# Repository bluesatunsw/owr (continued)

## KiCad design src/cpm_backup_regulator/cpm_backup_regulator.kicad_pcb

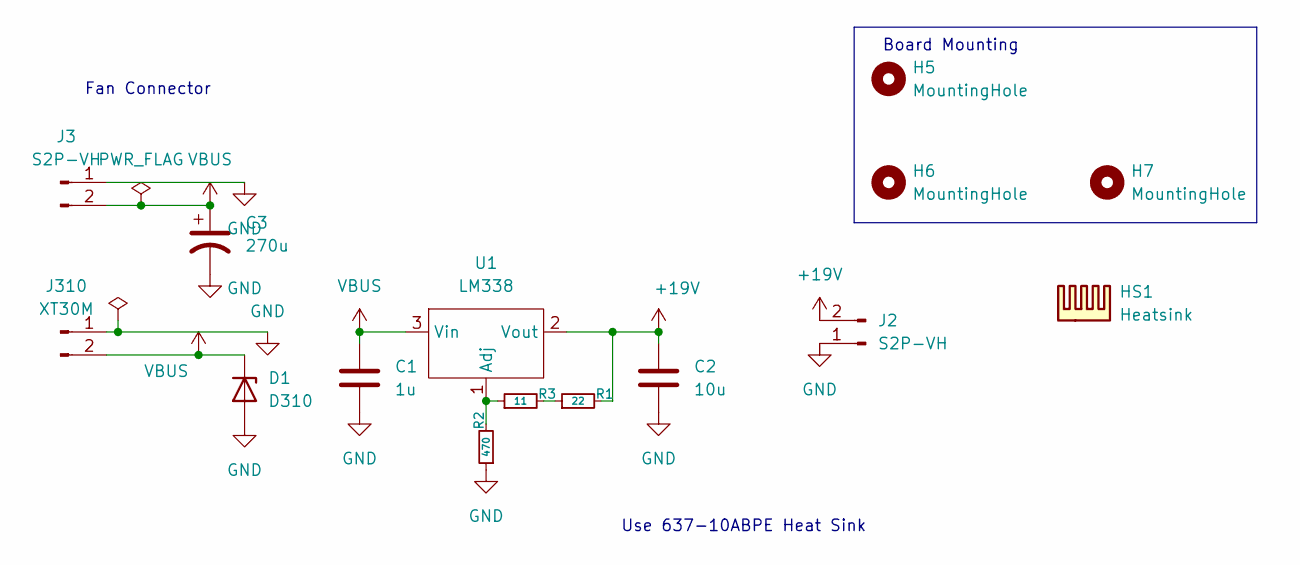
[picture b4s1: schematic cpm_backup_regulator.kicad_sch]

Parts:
C1: 1u; C_0805_2012Metric
C2: 10u; C_1210_3225Metric
C3: 270u; CP_Elec_10x10
D1: D310; D_SMF
H5, H6, H7: MountingHole; M2.5_Internal
HS1: Heatsink; Heatsink_Fischer_SK129-STS_42x25mm_2xDrill2.5mm
J2: S2P-VH; B2P-VH
J3: S2P-VH; BM02B-PASS
J310: XT30M; AMASS_XT30PW-M_1x02_P2.50mm_Horizontal
R1: 22; C_0402_1005Metric
R2: 470; C_0402_1005Metric
R3: 11; C_0402_1005Metric
U1: LM338; TO-220F-3_Vertical

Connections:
+19V: C2.1, J2.2, R1.2, U1.2 (Vout)
GND: C1.2, C2.2, C3.2, D1.2 (A), J2.1, J3.1, J310.1, R2.1
unnamed: R1.1, R3.2
unnamed: R2.2, R3.1, U1.1 (Adj)
VBUS: C1.1, C3.1, D1.1 (K), J3.2, J310.2, U1.3 (Vin)

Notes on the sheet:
Fan Connector
Board Mounting
Use 637-10ABPE Heat Sink

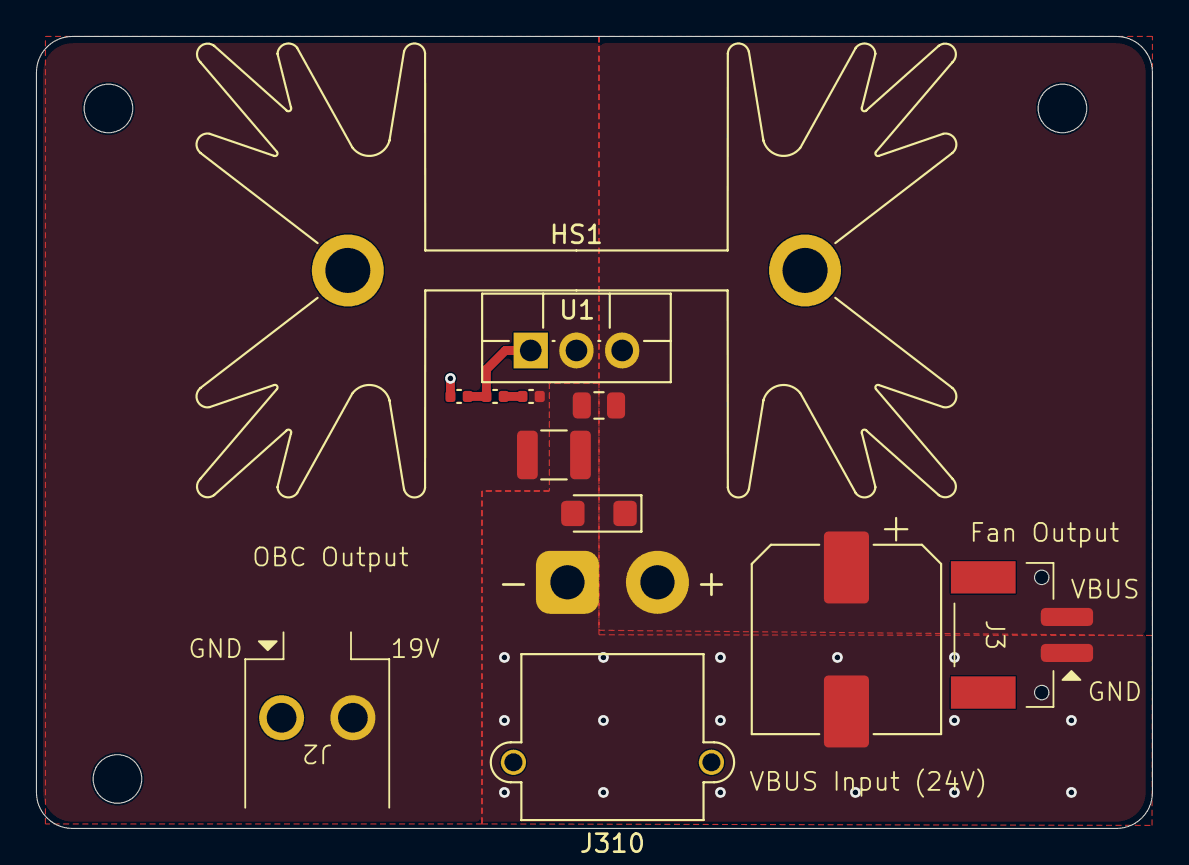
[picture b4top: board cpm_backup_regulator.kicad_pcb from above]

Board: 2 copper layers, 62.0 x 44.0 mm, 15 parts (0 on the bottom side), 5 nets.

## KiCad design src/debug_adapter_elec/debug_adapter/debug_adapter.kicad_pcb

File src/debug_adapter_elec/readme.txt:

STLink V3 clone: https://www.alibaba.com/product-detail/Weact-STLink-DAP-Link-ARM-debugger_1601206848066.html
STLink V2 clone: https://www.alibaba.com/product-detail/ST-LINK-V2-STM8-STM32-simulator_1601017055060.html

Connector to V3: JST-SH 10 pin horizontal - https://www.lcsc.com/product-detail/C160409.html
Connector to V2: 2x5 vertical keyed duponts - https://www.lcsc.com/product-detail/C358740.html
Connector to device under test (DUT): standard IDC6 connector permanently connected using epoxy - https://www.lcsc.com/product-detail/C42372553.html

more info on the github issue: https://github.com/bluesatunsw/owr-docs/issues/446

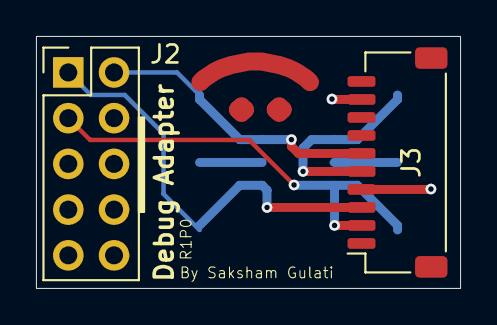
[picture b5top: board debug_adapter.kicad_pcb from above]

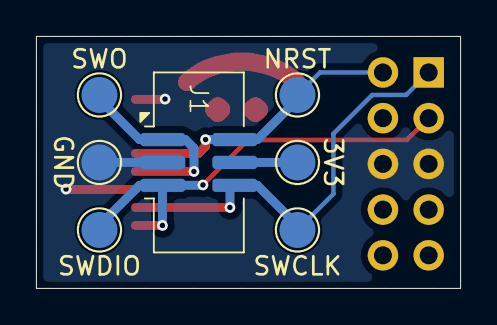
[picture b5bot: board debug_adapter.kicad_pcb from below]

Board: 2 copper layers, 23.6 x 14.0 mm, 9 parts (7 on the bottom side), 6 nets.

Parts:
3V3: TestPoint; TestPoint_Pad_D2.0mm
GND: TestPoint; TestPoint_Pad_D2.0mm
J1: Conn_02x03_Odd_Even; IDC6
J2: Conn_02x05_Odd_Even; PinHeader_2x05_P2.54mm_Vertical
J3: Conn_01x10; JST_SH_SM10B-SRSS-TB_1x10-1MP_P1.00mm_Horizontal
NRST: TestPoint; TestPoint_Pad_D2.0mm
SWCLK: TestPoint; TestPoint_Pad_D2.0mm
SWDIO: TestPoint; TestPoint_Pad_D2.0mm
SWO: TestPoint; TestPoint_Pad_D2.0mm

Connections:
/3V3: 3V3.1 (1_1), J1.4
/GND: GND.1 (1_1), J1.3, J2.5, J2.6, J3.4, J3.9
/NRST: J1.2, J2.2, J3.6, NRST.1 (1_1)
/SWCLK: J1.6, J2.1, J3.3, SWCLK.1 (1_1)
/SWDIO: J1.5, J2.3, J3.2, SWDIO.1 (1_1)
/SWO: J1.1, J3.5, SWO.1 (1_1)

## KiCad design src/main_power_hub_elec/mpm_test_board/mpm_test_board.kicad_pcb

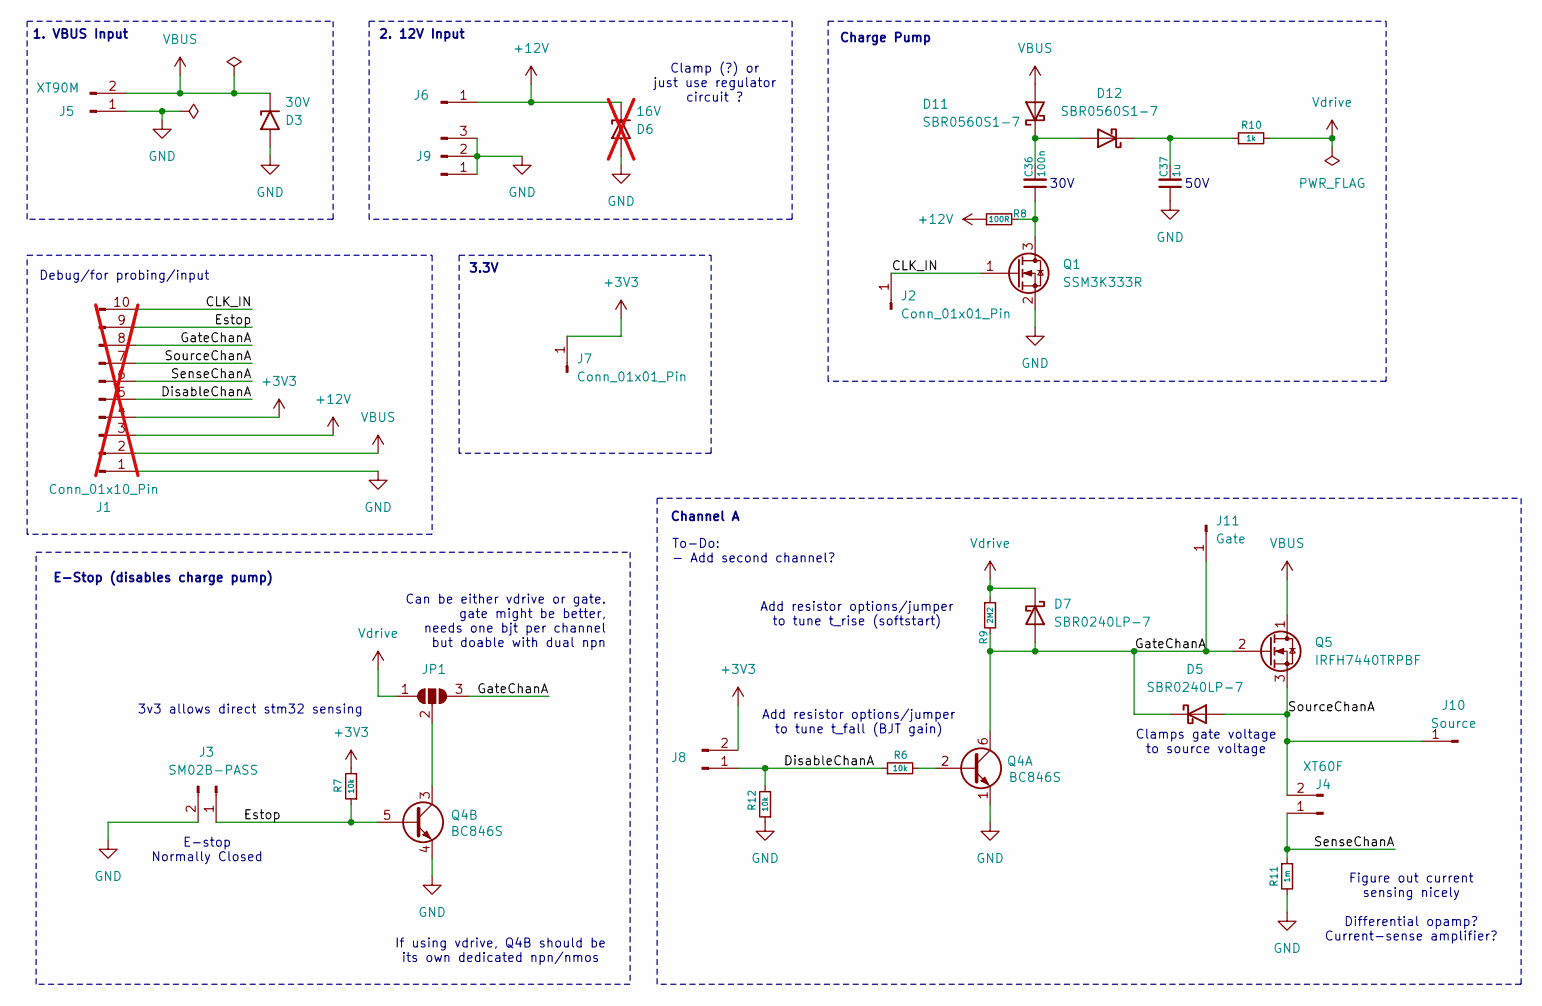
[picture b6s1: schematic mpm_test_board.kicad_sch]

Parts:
C36: 100n; C_0603_1608Metric
C37: 1u; C_1206_3216Metric
D3: 30V; D_SMF
D5, D7: SBR0240LP-7; D_SOD-882D
D6: 16V; not fitted
D11, D12: SBR0560S1-7; D_SOD-123
J1: Conn_01x10_Pin; PinHeader_1x10_P2.54mm_Vertical; not fitted
J2, J7: Conn_01x01_Pin; PinHeader_1x01_P2.54mm_Vertical
J3: SM02B-PASS
J4: XT60F; AMASS_XT60PW-F_1x02_P7.20mm_Horizontal
J5: XT90M; AMASS_XT90PW-M_1x02_P10.90mm_Horizontal
J6: PinHeader_1x01_P2.54mm_Vertical
J8: PinHeader_1x02_P2.54mm_Vertical
J9: Conn_01x10_Pin; PinHeader_1x03_P2.54mm_Vertical
J10: Source; PinHeader_1x01_P2.54mm_Vertical
J11: Gate; PinHeader_1x01_P2.54mm_Vertical
JP1: SolderJumper_3_Open; SolderJumper-3_P1.3mm_Open_Pad1.0x1.5mm_NumberLabels
Q1: SSM3K333R; SOT-23-3
Q4: BC846S; SOT-363
Q5: IRFH7440TRPBF; PQFN_5x6mm_E_DGS
R6, R7, R12: 10k; R_0402_1005Metric
R8: 100R; R_0402_1005Metric
R9: 2M2; R_0402_1005Metric
R10: 1k; R_0402_1005Metric
R11: 1m; R_2512_6332Metric

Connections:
+3V3: J1.4, J7.1 (Pin_1_1), J8.2, R7.2
+12V: D6.1 (A1), J1.3, J6.1 (Pin_1_1), R8.1
/CLK_IN: J1.10, J2.1 (Pin_1_1), Q1.1 (G)
/DisableChanA: J1.5, J8.1, R6.1, R12.2
/Estop: J1.9, J3.1, Q4.5 (B2), R7.1
/GateChanA: D5.1 (K), D7.2 (A), J1.8, J11.1 (Pin_1_1), JP1.3 (B), Q4.6 (C1), Q5.2 (G), R9.2
/SenseChanA: J1.6, J4.1, R11.1
/SourceChanA: D5.2 (A), J1.7, J4.2, J10.1 (Pin_1_1), Q5.3 (S)
GND: C37.1, D3.2 (A2), D6.2 (A2), J1.1, J3.2, J5.1, J9.1, J9.2, J9.3, Q1.2 (S), Q4.1 (E1), Q4.4 (E2), R11.2, R12.1
unnamed: C36.2, D11.1 (K), D12.2 (A)
unnamed: C37.2, D12.1 (K), R10.1
unnamed: JP1.2 (C), Q4.3 (C2)
unnamed: C36.1, Q1.3 (D), R8.2
unnamed: Q4.2 (B1), R6.2
VBUS: D3.1 (A1), D11.2 (A), J1.2, J5.2, Q5.1 (D)
Vdrive: D7.1 (K), JP1.1 (A), R9.1, R10.2

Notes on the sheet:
E-Stop (disables charge pump)
E-stop Normally Closed
3.3V
Figure out current sensing nicely Differential opamp? Current-sense amplifier?
Clamp (?) or just use regulator circuit ?
2. 12V Input
Charge Pump
50V
3v3 allows direct stm32 sensing
Debug/for probing/input
Can be either vdrive or gate. gate might be better, needs one bjt per channel but doable with dual npn
Add resistor options/jumper to tune t_fall (BJT gain)
30V
Channel A
1. VBUS Input
If using vdrive, Q4B should be its own dedicated npn/nmos
Clamps gate voltage to source voltage
Add resistor options/jumper to tune t_rise (softstart)
To-Do: - Add second channel?

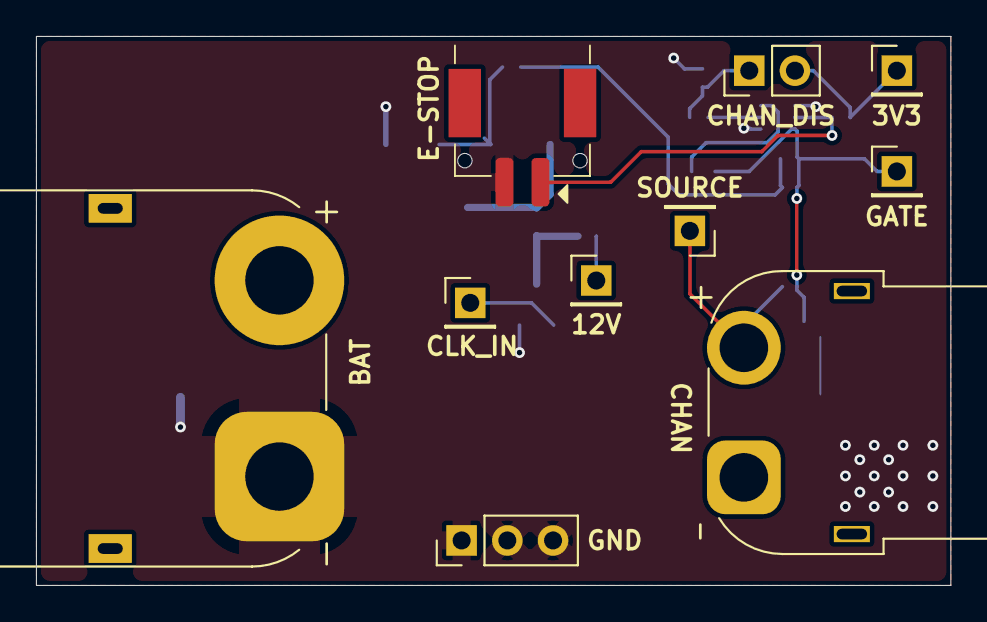
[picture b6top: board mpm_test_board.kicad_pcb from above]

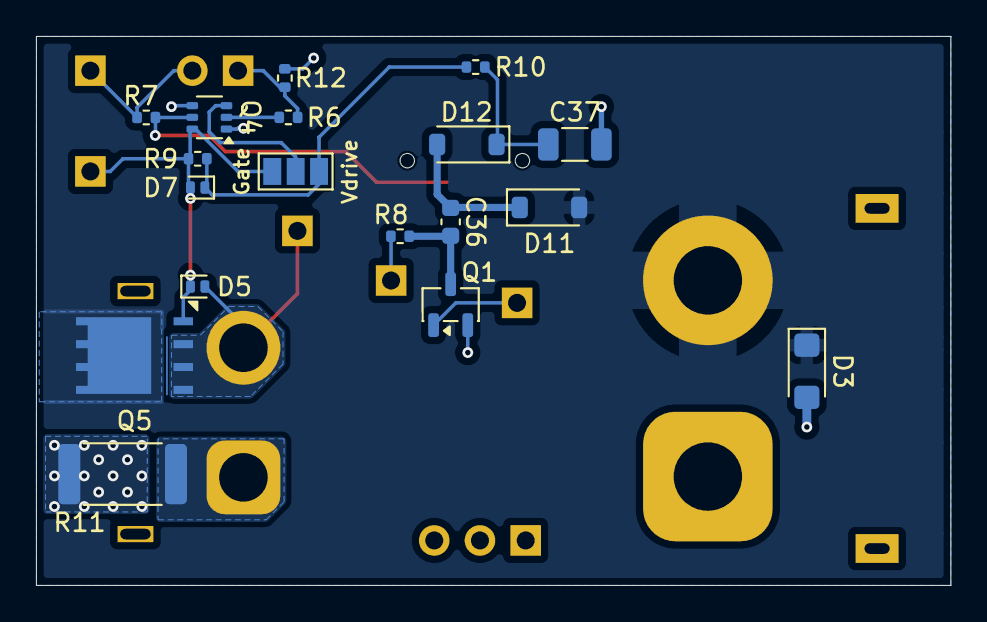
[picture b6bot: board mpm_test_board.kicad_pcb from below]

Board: 2 copper layers, 50.8 x 30.5 mm, 28 parts (18 on the bottom side), 16 nets.

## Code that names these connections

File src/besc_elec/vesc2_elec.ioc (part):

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Mcu.Name=STM32G474R(B-C-E)Tx
Mcu.Package=LQFP64
Mcu.UserName=STM32G474RBTx
PA0.GPIOParameters=GPIO_Label
PA0.GPIO_Label=HALL_W
PA0.Signal=S_TIM5_CH1
PA1.GPIOParameters=GPIO_Label
PA1.GPIO_Label=HALL_V
PA1.Signal=S_TIM5_CH2
PA10.GPIOParameters=GPIO_Label
PA10.GPIO_Label=ARGB
PA10.Signal=S_TIM1_CH3
PA11.GPIOParameters=GPIO_Label
PA11.GPIO_Label=CAN_RX
PA11.Mode=FDCAN_Activate
PA11.Signal=FDCAN1_RX
PA12.GPIOParameters=GPIO_Label
PA12.GPIO_Label=CAN_TX
PA12.Mode=FDCAN_Activate
PA12.Signal=FDCAN1_TX
PA13.Mode=Trace_Asynchronous_SW
PA13.Signal=SYS_JTMS-SWDIO
PA14.Mode=Trace_Asynchronous_SW
PA14.Signal=SYS_JTCK-SWCLK
PA15.GPIOParameters=GPIO_Label
PA15.GPIO_Label=I2C1_SCL
PA15.Mode=I2C
PA15.Signal=I2C1_SCL
PA2.GPIOParameters=GPIO_Label
PA2.GPIO_Label=HALL_U
PA2.Signal=S_TIM5_CH3
PA3.GPIOParameters=GPIO_Label
PA3.GPIO_Label=QSPI_CLK
PA3.Mode=Single Bank 1
PA3.Signal=QUADSPI1_CLK
PA4.GPIOParameters=GPIO_Label
PA4.GPIO_Label=DRV_CAL
PA4.Signal=GPIO_Output
PA5.GPIOParameters=GPIO_Label
PA5.GPIO_Label=PHS_B
PA5.Mode=IN13-Single-Ended
PA5.Signal=ADC2_IN13
PA6.GPIOParameters=GPIO_Label
PA6.GPIO_Label=QSPI_IO3
PA6.Mode=Single Bank 1
PA6.Signal=QUADSPI1_BK1_IO3
PA7.GPIOParameters=GPIO_Label
PA7.GPIO_Label=QSPI_IO2
PA7.Mode=Single Bank 1
PA7.Signal=QUADSPI1_BK1_IO2
PA8.GPIOParameters=GPIO_Label
PA8.GPIO_Label=SENS_C
PA8.Mode=IN1-Single-Ended
PA8.Signal=ADC5_IN1
PA9.GPIOParameters=GPIO_Label
PA9.GPIO_Label=PHS_C
PA9.Mode=IN2-Single-Ended
PA9.Signal=ADC5_IN2
PB0.GPIOParameters=GPIO_Label
PB0.GPIO_Label=QSPI_IO1
PB0.Mode=Single Bank 1
PB0.Signal=QUADSPI1_BK1_IO1
PB1.GPIOParameters=GPIO_Label
PB1.GPIO_Label=QSPI_IO0
PB1.Mode=Single Bank 1
PB1.Signal=QUADSPI1_BK1_IO0
PB10.GPIOParameters=GPIO_Label
PB10.GPIO_Label=DRV_FLT
PB10.Mode=Fault_Enable3
PB10.Signal=HRTIM1_FLT3
PB11.GPIOParameters=GPIO_Label
PB11.GPIO_Label=QSPI_NCS
PB11.Mode=Single Bank 1
PB11.Signal=QUADSPI1_BK1_NCS
PB12.GPIOParameters=GPIO_Label
PB12.GPIO_Label=PWM_L3
PB12.Mode=Output_TC1TC2
PB12.Signal=HRTIM1_CHC1
PB13.GPIOParameters=GPIO_Label
PB13.GPIO_Label=PWM_H3
PB13.Mode=Output_TC1TC2
PB13.Signal=HRTIM1_CHC2
PB14.GPIOParameters=GPIO_Label
PB14.GPIO_Label=SENS_A
PB14.Mode=IN5-Single-Ended
PB14.Signal=ADC1_IN5
PB15.GPIOParameters=GPIO_Label
PB15.GPIO_Label=VSENS
PB15.Mode=IN5-Single-Ended
PB15.Signal=ADC4_IN5
PB3.Mode=Trace_Asynchronous_SW
PB3.Signal=SYS_JTDO-SWO
PB5.GPIOParameters=GPIO_Label
PB5.GPIO_Label=DRV_EN
PB5.Signal=GPIO_Output
PB6.GPIOParameters=GPIO_Label
PB6.GPIO_Label=X1
PB6.Signal=GPIO_Input
PB7.GPIOParameters=GPIO_Label
PB7.GPIO_Label=X2
PB7.Signal=GPIO_Input
PB9.GPIOParameters=GPIO_Label
PB9.GPIO_Label=I2C1_SDA
PB9.Mode=I2C
PB9.Signal=I2C1_SDA
PC0.GPIOParameters=GPIO_Label
PC0.GPIO_Label=PHS_A
PC0.Mode=IN6-Single-Ended
PC0.Signal=ADC1_IN6
PC10.GPIOParameters=GPIO_Label
PC10.GPIO_Label=ENC_SCK
PC10.Mode=Full_Duplex_Master
PC10.Signal=SPI3_SCK
PC11.GPIOParameters=GPIO_Label
PC11.GPIO_Label=ENC_MISO
PC11.Mode=Full_Duplex_Master
PC11.Signal=SPI3_MISO
PC12.GPIOParameters=GPIO_Label
PC12.GPIO_Label=ENC_MOSI
PC12.Mode=Full_Duplex_Master
PC12.Signal=SPI3_MOSI
PC2.GPIOParameters=GPIO_Label
PC2.GPIO_Label=TEMP_MOT
PC2.Mode=IN8-Single-Ended
PC2.Signal=ADC1_IN8
PC3.GPIOParameters=GPIO_Label
PC3.GPIO_Label=TEMP_BRD
PC3.Mode=IN9-Single-Ended
PC3.Signal=ADC2_IN9
PC4.GPIOParameters=GPIO_Label
PC4.GPIO_Label=SENS_B
PC4.Mode=IN5-Single-Ended
PC4.Signal=ADC2_IN5
PC6.GPIOParameters=GPIO_Label
PC6.GPIO_Label=PWM_L2
PC6.Mode=Output_TF1TF2
PC6.Signal=HRTIM1_CHF1
PC7.GPIOParameters=GPIO_Label
PC7.GPIO_Label=PWM_H2
PC7.Mode=Output_TF1TF2
PC7.Signal=HRTIM1_CHF2
PC8.GPIOParameters=GPIO_Label
PC8.GPIO_Label=PWM_L1
PC8.Mode=Output_TE1TE2
PC8.Signal=HRTIM1_CHE1
PC9.GPIOParameters=GPIO_Label
PC9.GPIO_Label=PWM_H1
PC9.Mode=Output_TE1TE2
PC9.Signal=HRTIM1_CHE2
PD2.GPIOParameters=GPIO_Label
PD2.GPIO_Label=ENC_CS
PD2.Signal=GPIO_Output
PF0-OSC_IN.Mode=HSE-External-Oscillator
PF0-OSC_IN.Signal=RCC_OSC_IN
PF1-OSC_OUT.Mode=HSE-External-Oscillator
PF1-OSC_OUT.Signal=RCC_OSC_OUT
RCC.HSE_VALUE=24000000
RCC.SYSCLKFreq_VALUE=170000000
RCC.SYSCLKSource=RCC_SYSCLKSOURCE_PLLCLK
board=custom

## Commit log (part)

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2026-06-06 start spm firmware folder and init project
2026-06-20 Remove fun :(
2026-06-20 started on bringup code
2026-06-20 Firmware`1
2026-06-24 code + mx file fix
